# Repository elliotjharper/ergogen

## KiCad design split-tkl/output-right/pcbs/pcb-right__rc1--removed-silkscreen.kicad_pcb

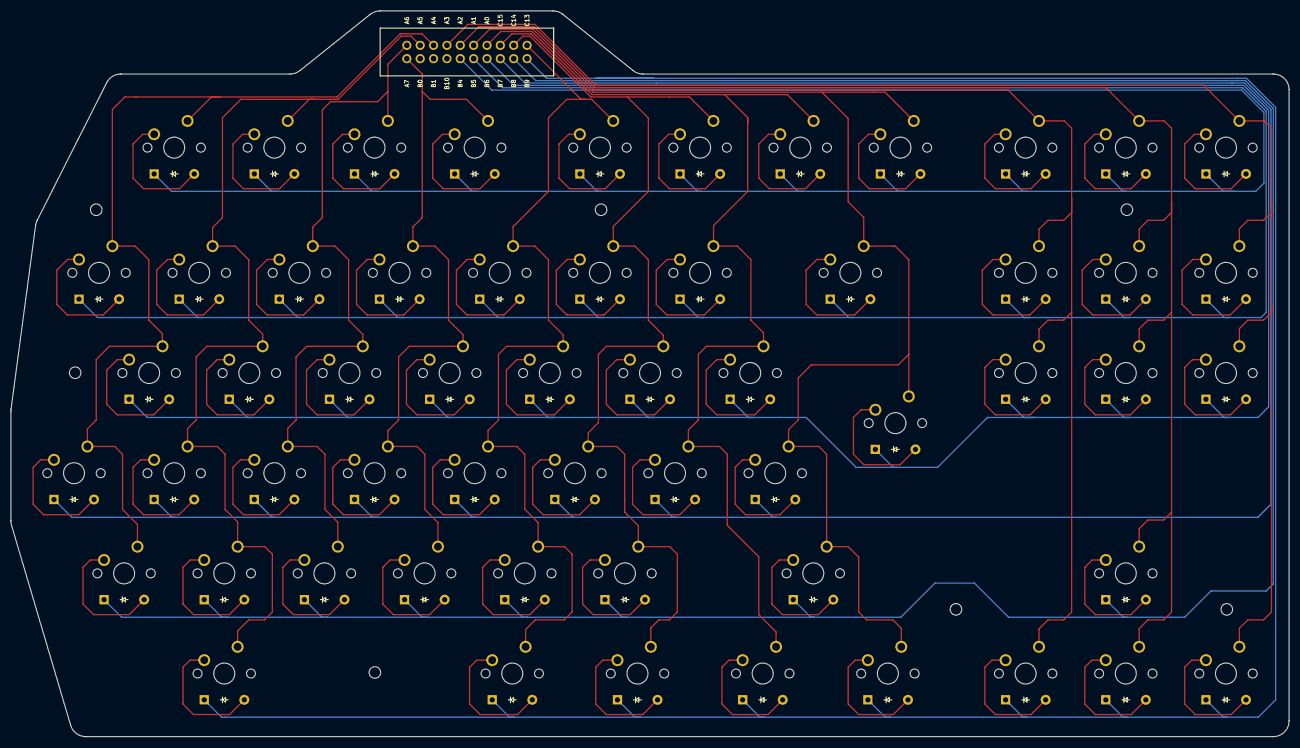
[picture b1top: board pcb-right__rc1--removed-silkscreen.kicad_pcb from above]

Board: 2 copper layers, 243.1 x 138.0 mm, 122 parts (0 on the bottom side), 74 nets.

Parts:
BH1: IdcBoxHeader
D1, D2, D3, D4, D5, D6, D7, D8, D9, D10, D11, D12, D13, D14, D15, D16, D17, D18, D19, D20, D21, D22, D23, D24, D25, D26, D27, D28, D29, D30, D31, D32, D33, D34, D35, D36, D37, D38, D39, D40, D41, D42, D43, D44, D45, D46, D47, D48, D49, D50, D51, D52, D53, D54, D55, D56, D57: ComboDiode
MH1, MH2, MH3, MH4, MH5, MH6, MH7: mounting_hole_npth
S1, S2, S3, S4, S5, S6, S7, S8, S9, S10, S11, S12, S13, S14, S15, S16, S17, S18, S19, S20, S21, S22, S23, S24, S25, S26, S27, S28, S29, S30, S31, S32, S33, S34, S35, S36, S37, S38, S39, S40, S41, S42, S43, S44, S45, S46, S47, S48, S49, S50, S51, S52, S53, S54, S55, S56, S57: MX

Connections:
A0: BH1.17, S8.1, S23.1, S30.1, S38.1, S46.1, S47.1
A1: BH1.16, S39.1, S48.1, S49.1, S50.1
A2: BH1.15, S40.1, S51.1, S52.1, S53.1, S54.1
A3: BH1.14, S41.1, S55.1, S56.1, S57.1
A4: BH1.13, S1.1, S9.1, S16.1, S24.1, S31.1
A5: BH1.12, S2.1, S10.1, S17.1, S25.1, S32.1, S42.1
A6: BH1.11, S3.1, S11.1, S18.1, S26.1, S33.1
A7: BH1.1, S4.1, S12.1, S19.1, S27.1, S34.1
B4: BH1.5, D31.1, D32.1, D33.1, D34.1, D35.1, D36.1, D37.1, D38.1, D39.1, D40.1, D41.1
B5: BH1.6, D1.1, D2.1, D3.1, D4.1, D5.1, D6.1, D7.1, D8.1, D50.1, D54.1, D57.1
B6: BH1.7, D9.1, D10.1, D11.1, D12.1, D13.1, D14.1, D15.1, D47.1, D49.1, D53.1, D56.1
B7: BH1.8, D16.1, D17.1, D18.1, D19.1, D20.1, D21.1, D22.1, D23.1
B8: BH1.9, D24.1, D25.1, D26.1, D27.1, D28.1, D29.1, D30.1, D52.1
B9: BH1.10, D42.1, D43.1, D44.1, D45.1, D46.1, D48.1, D51.1, D55.1
C13: BH1.20, S5.1, S13.1, S20.1, S28.1, S35.1, S43.1
C14: BH1.19, S6.1, S14.1, S21.1, S29.1, S36.1, S44.1
C15: BH1.18, S7.1, S15.1, S22.1, S37.1, S45.1
cap_i8: D19.2, S19.2
cap_minus: D22.2, S22.2
cap_o9: D20.2, S20.2
cap_p10: D21.2, S21.2
cap_plus: D23.2, S23.2
cap_t5: D16.2, S16.2
cap_u7: D18.2, S18.2
cap_y6: D17.2, S17.2
f5_only: D31.2, S31.2
f6_only: D32.2, S32.2
f7_only: D33.2, S33.2
f8_only: D34.2, S34.2
f9_only: D35.2, S35.2
f10_only: D36.2, S36.2
f11_only: D37.2, S37.2
f12_only: D38.2, S38.2
fn_only: D44.2, S44.2
left_arrowLower: D48.2, S48.2
left_delRow: D49.2, S49.2
left_insertRow: D50.2, S50.2
middle_arrowLower: D51.2, S51.2
middle_arrowUpper: D52.2, S52.2
middle_delRow: D53.2, S53.2
middle_insertRow: D54.2, S54.2
num_backspace: D8.2, S8.2
num_i8: D3.2, S3.2
num_minus: D6.2, S6.2
num_o9: D4.2, S4.2
num_p10: D5.2, S5.2
num_plus: D7.2, S7.2
num_u7: D2.2, S2.2
num_y6: D1.2, S1.2
only_only: D47.2, S47.2
pause_only: D41.2, S41.2
print_only: D39.2, S39.2
rAlt_only: D43.2, S43.2
rClick_only: D45.2, S45.2
rCtrl_only: D46.2, S46.2
right_arrowLower: D55.2, S55.2
right_delRow: D56.2, S56.2
right_insertRow: D57.2, S57.2
scroll_only: D40.2, S40.2
shift_i8: D26.2, S26.2
shift_minus: D29.2, S29.2
shift_o9: D27.2, S27.2
shift_p10: D28.2, S28.2
shift_plus: D30.2, S30.2
shift_u7: D25.2, S25.2
shift_y6: D24.2, S24.2
space_only: D42.2, S42.2
tab_i8: D11.2, S11.2
tab_minus: D14.2, S14.2
tab_o9: D12.2, S12.2
tab_p10: D13.2, S13.2
tab_plus: D15.2, S15.2
tab_u7: D10.2, S10.2
tab_y6: D9.2, S9.2

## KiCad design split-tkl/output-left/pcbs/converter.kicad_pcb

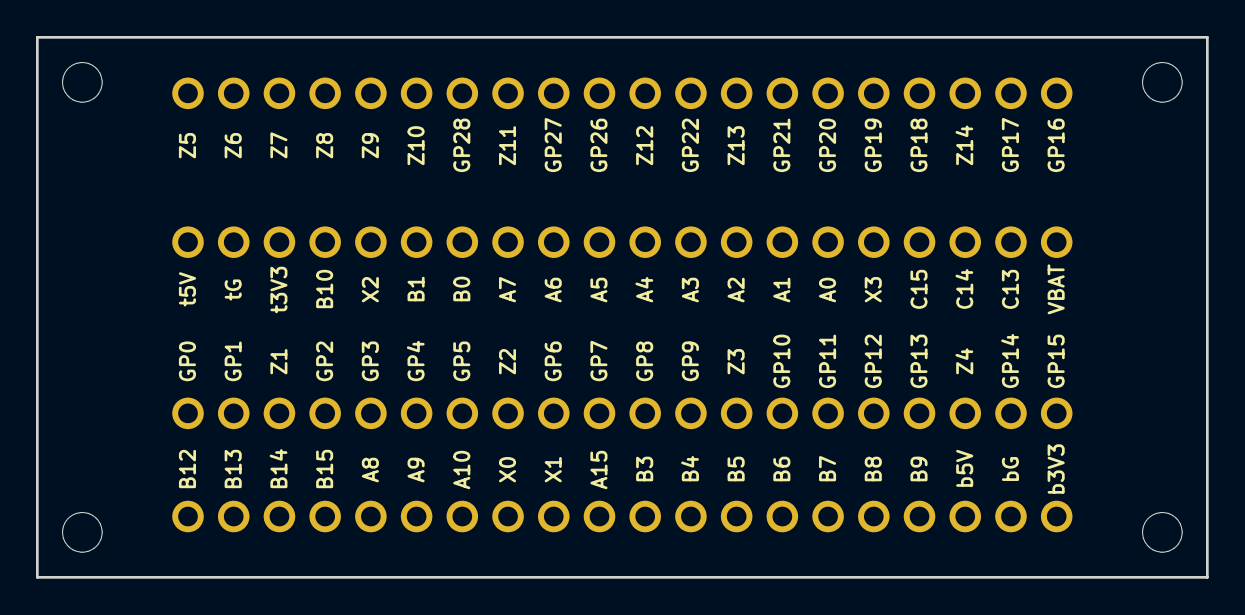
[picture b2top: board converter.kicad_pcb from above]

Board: 2 copper layers, 65.0 x 30.0 mm, 6 parts (0 on the bottom side), 24 nets, no tracks yet.

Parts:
MCU1: Blackpill
MCU2: Pico
MH1, MH2, MH3, MH4: mounting_hole_npth

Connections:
A0: MCU1.A0, MCU2.GP16
A1: MCU1.A1, MCU2.GP17
A2: MCU1.A2, MCU2.GP18
A3: MCU1.A3, MCU2.GP19
A4: MCU1.A4, MCU2.GP20
A5: MCU1.A5, MCU2.GP21
A6: MCU1.A6, MCU2.GP22
A7: MCU1.A7, MCU2.GP26
A8: MCU1.A8, MCU2.GP4
A9: MCU1.A9, MCU2.GP5
A10: MCU1.A10, MCU2.GP6
B4: MCU1.B4, MCU2.GP7
B5: MCU1.B5, MCU2.GP8
B6: MCU1.B6, MCU2.GP9
B7: MCU1.B7, MCU2.GP10
B8: MCU1.B8, MCU2.GP11
B9: MCU1.B9, MCU2.GP12
B12: MCU1.B12, MCU2.GP0
B13: MCU1.B13, MCU2.GP1
B14: MCU1.B14, MCU2.GP2
B15: MCU1.B15, MCU2.GP3
C13: MCU1.C13, MCU2.GP15
C14: MCU1.C14, MCU2.GP14
C15: MCU1.C15, MCU2.GP13

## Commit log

2025-02-20 Added a custom outline shape "mxhole"
2025-03-01 worked on a bunch of custom footprints
2025-03-01 big progress
2025-03-02 fixed blackpill footprint rewrite
2025-03-02 Rewrote blackpill to make basically everything parameterised from pin keys
2025-03-02 Noted the pin selection and sorted the nets from controller to cols and rows. need to sort the nets from controller to header to row
2025-03-02 wired nets from controller to header and through to rows
2025-03-05 Nearly final!
2025-03-05 Added all the traces for the left pcb, need to remove the on board pads
2025-03-08 Routed version with the smd pads removed
2025-03-08 Stopped pth's from being on the silk screen layer and creating drc errors because it was printing the hole into the silkscreen. Also fixed my custom blackpill footprint that created the problem
2025-03-08 committing the rc1 that i am getting made
2025-03-08 Made the diode footprint parameterised. Revived the return key in the right yaml. Added mounting holes to the right yaml
2025-03-08 On the right hand keeb, adjusted the net cols for the bottom 2 rows to fix the matrix
2025-03-08 Committed the files that i sent off for production
2025-03-09 Starting work on final plate and preparing for case
2025-03-09 Renamed the folder from split-left to split-tkl as it does contain the right side too
2025-03-09 Built plate test into ergogen and brought in the jscad cli and then added a script to run ergogen and then use jscad on the output to get stl's
2025-03-20 Got QMK running, wrote diary for how i did it and started a copy of the keyboard source
2025-03-20 Did a working 2 row keymap and matrix
2025-03-20 Add to outline
2025-03-21 Wrote the matrix out in tabular form ready to write a qmk keyboard
2025-03-21 Wrote the matrix into the keyboard.json and the keymap.c file
2025-03-21 checking in the compilation result of the currently checked in keymap and keyboard json
2025-03-21 Made valid json
2025-03-22 converted keyboard json from being specified in cols to specified in rows
2025-03-23 Pin mapping between controllers
2025-03-23 Changed pin selection to work with pi pico limits
2025-03-23 Starting on actual case
2025-03-30 Updated diary
2025-03-30 Incorporated the electronics footprints into an outline so that I could CAD up a case
2025-04-03 Adding a case outline so I can CAD up a case for the right hand side
2025-04-13 Remapped the pins
2025-04-13 Described pi pin
2025-04-13 Updated the firmware
2025-04-13 added a converter pcb and wrote the footprint for a pi pco and sorted mapping between the pico and the blackpill
2025-05-07 Fixed the keycode for the left backslash
2025-10-21 Committing old changes
2025-10-21 Updated the pico footprint and setup the the mount holes
2025-10-21 Clean break to start low profile version
2025-11-01 Renamed again
2025-11-04 Started a gateronmx33 footprint using a copy of mx as a starting point
2025-11-04 Added an stl viewer for the output
2025-11-04 Supporting preview dxf files
2025-11-04 progress (gateron mx33 footprint right) NEXT: add diodes to mx33 footprint
2025-11-04 Almost got a gateron mx33 with diodes complete, pads and labellling is good but nets for the circuit just need figuring out (see TODO)
2025-11-04 swapped pi pico in
2025-11-05 Set the server up to watch the yaml files and auto rebuild the output as the yaml files are changed. Also got the left yaml much further (sorted the pcb outline and sorted the mounting holes)
